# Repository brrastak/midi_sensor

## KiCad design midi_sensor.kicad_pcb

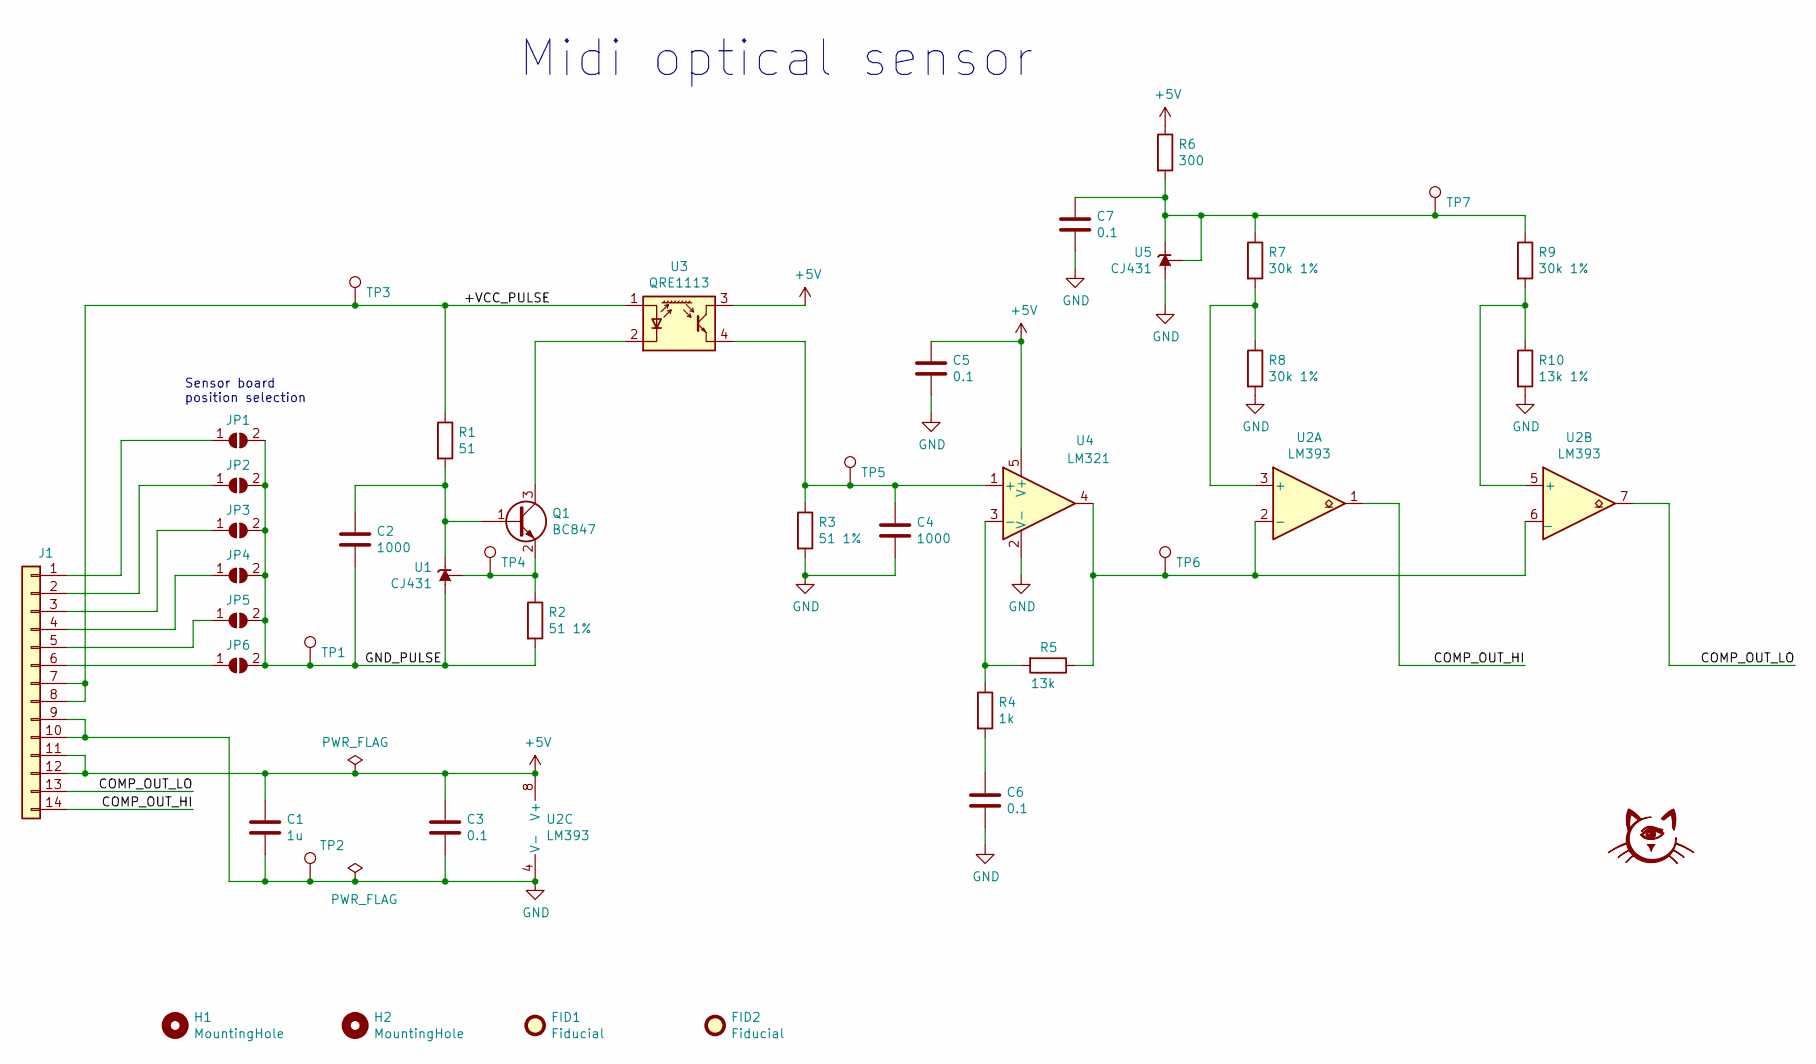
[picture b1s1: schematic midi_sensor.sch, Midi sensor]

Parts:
C1: 1u; C_0603_1608Metric
C2, C4: 1000; C_0603_1608Metric
C3, C5, C6, C7: 0.1; C_0603_1608Metric
FID1, FID2: Fiducial; Fiducial_1mm_Mask2mm
G1: LOGO; stamp
H1, H2: MountingHole; hole_D2mm
J1: Conn_01x14; edge_connector
JP1, JP2, JP3, JP4, JP5, JP6: SolderJumper_2_Open; SolderJumper-2_P1.3mm_Open_RoundedPad1.0x1.5mm
Q1: BC847; SOT-23
R1: 51; R_0603_1608Metric
R2, R3: 51 1%; R_0603_1608Metric
R4: 1k; R_0603_1608Metric
R5: 13k; R_0603_1608Metric
R6: 300; R_0603_1608Metric
R7, R8, R9: 30k 1%; R_0603_1608Metric
R10: 13k 1%; R_0603_1608Metric
TP1, TP2, TP3, TP4, TP5, TP6, TP7: TestPoint; TP
U1, U5: CJ431; SOT-23
U2: LM393; SOIC-8_3.9x4.9mm_P1.27mm
U3: QRE1113; OnSemi_CASE100CY
U4: LM321; SOT-23-5

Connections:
+5V: C1.1, C3.1, C5.1, J1.11, J1.12, R6.1, U2.8 (V+), U3.3, U4.5 (V+)
/+VCC_PULSE: J1.7, J1.8, R1.1, TP3.1, U3.1 (A)
/COMP_OUT_HI: J1.14, U2.1
/COMP_OUT_LO: J1.13, U2.7
/GND_PULSE: C2.2, JP1.2 (B), JP2.2 (B), JP3.2 (B), JP4.2 (B), JP5.2 (B), JP6.2 (B), R2.2, TP1.1, U1.3 (A)
GND: C1.2, C3.2, C4.2, C5.2, C6.2, C7.2, J1.9, J1.10, R3.2, R8.2, R10.2, TP2.1, U2.4 (V-), U4.2 (V-), U5.3 (A)
unnamed: C2.1, Q1.1 (B), R1.2, U1.2 (K)
unnamed: C4.1, R3.1, TP5.1, U3.4, U4.1 (+)
unnamed: C6.1, R4.2
unnamed: C7.1, R6.2, R7.1, R9.1, TP7.1, U5.1 (REF), U5.2 (K)
unnamed: J1.1, JP1.1 (A)
unnamed: J1.2, JP2.1 (A)
unnamed: J1.3, JP3.1 (A)
unnamed: J1.4, JP4.1 (A)
unnamed: J1.5, JP5.1 (A)
unnamed: J1.6, JP6.1 (A)
unnamed: Q1.2 (E), R2.1, TP4.1, U1.1 (REF)
unnamed: Q1.3 (C), U3.2 (K)
unnamed: R4.1, R5.2, U4.3 (-)
unnamed: R5.1, TP6.1, U2.2 (-), U2.6 (_), U4.4
unnamed: R7.2, R8.1, U2.3 (+)
unnamed: R9.2, R10.1, U2.5 (+)

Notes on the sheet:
Sensor board position selection
Midi optical sensor

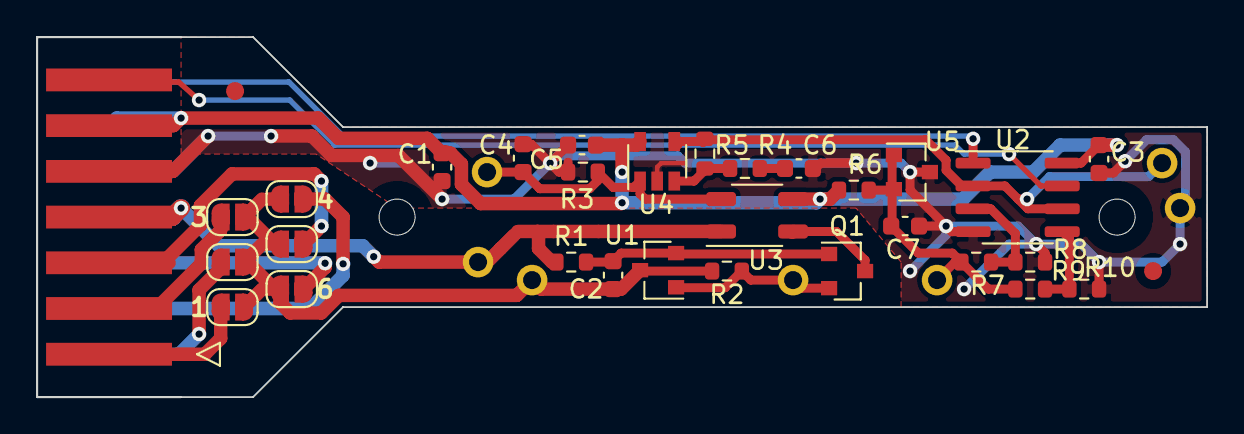
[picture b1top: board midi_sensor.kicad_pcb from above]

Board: 2 copper layers, 65.0 x 20.0 mm, 42 parts (1 on the bottom side), 22 nets.

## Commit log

2021-08-30 Create empty
